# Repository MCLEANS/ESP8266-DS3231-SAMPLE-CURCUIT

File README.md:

# ESP8266-DS3231-SAMPLE-CURCUIT
A sample circuit for SMD ESP8266 and  DS3231 Implementation.

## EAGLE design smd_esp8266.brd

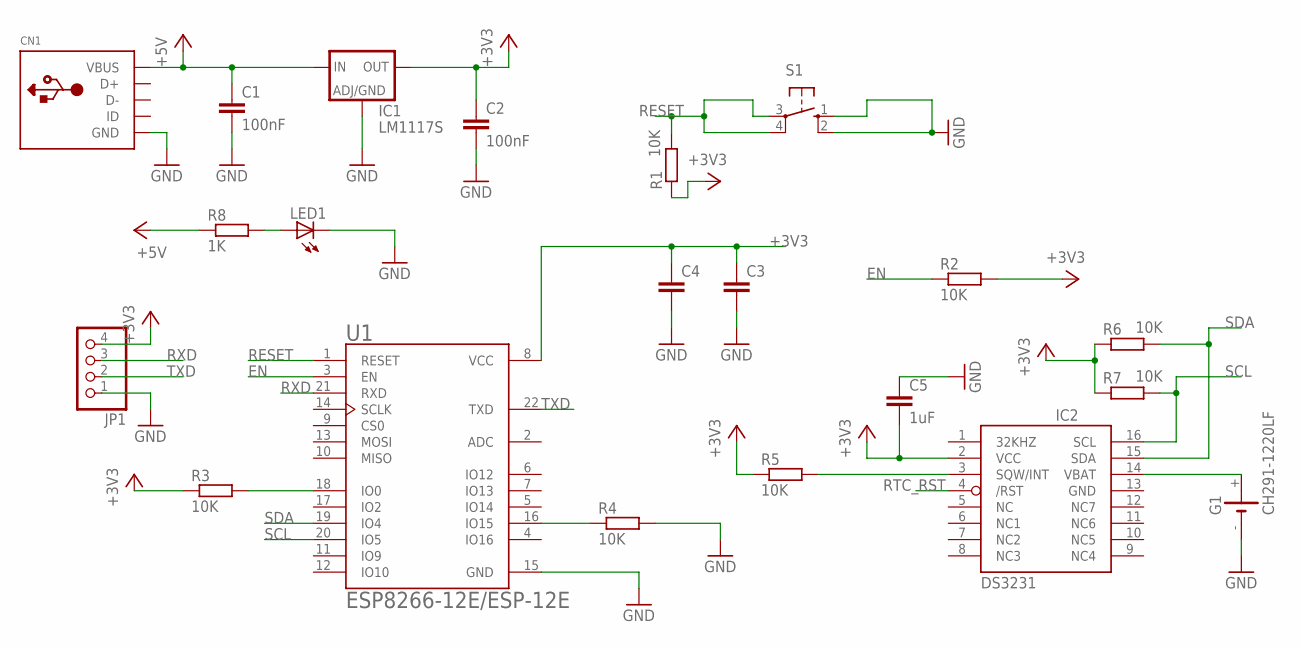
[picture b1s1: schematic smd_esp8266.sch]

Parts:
C1, C2: 100nF; C0805
C3, C4: C-EUC0805; C0805
C5: 1uF; C0805
CN1: USBMINIB; USB-MINIB
G1: CH291-1220LF
IC1: LM1117S; SOT223
IC2: DS3231/SO; SO16W
JP1: PINHD-1X4; 1X04
LED1: LEDCHIP-LED0805; CHIP-LED0805
R1, R2, R3, R4, R5, R6, R7: 10K; R0805
R8: 1K; R0805
S1: 10-XX; B3F-10XX
U1: ESP8266-12E/ESP-12E; XCVR_ESP8266-12E/ESP-12E

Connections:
+3V3: C2.1, C3.1, C4.1, C5.2, IC1.2 (OUT), IC1.4 (OUT), IC2.2 (VCC), JP1.4, R1.1, R2.2, R3.1, R5.1, R6.1, R7.1, U1.8 (VCC)
+5V: C1.1, CN1.VBUS, IC1.3 (IN), R8.1
EN: R2.1, U1.3 (EN)
GND: C1.2, C2.2, C3.2, C4.2, C5.1, CN1.GND, G1.-, IC1.1 (ADJ), IC2.13 (GND), JP1.1, LED1.C, R4.2, S1.1 (S), S1.2 (S1), U1.15 (GND)
unnamed: R3.2, U1.18 (IO0)
unnamed: R4.1, U1.16 (IO15)
unnamed: IC2.3 (SQW/INT), R5.2
unnamed: G1.+, IC2.14 (VBAT)
unnamed: LED1.A, R8.2
RESET: R1.2, S1.3, S1.4 (P1), U1.1 (RESET)
RTC_RST: IC2.4 (/RST)
RXD: JP1.3, U1.21 (RXD)
SCL: IC2.16 (SCL), R7.2, U1.20 (IO5)
SDA: IC2.15 (SDA), R6.2, U1.19 (IO4)
TXD: JP1.2, U1.22 (TXD)

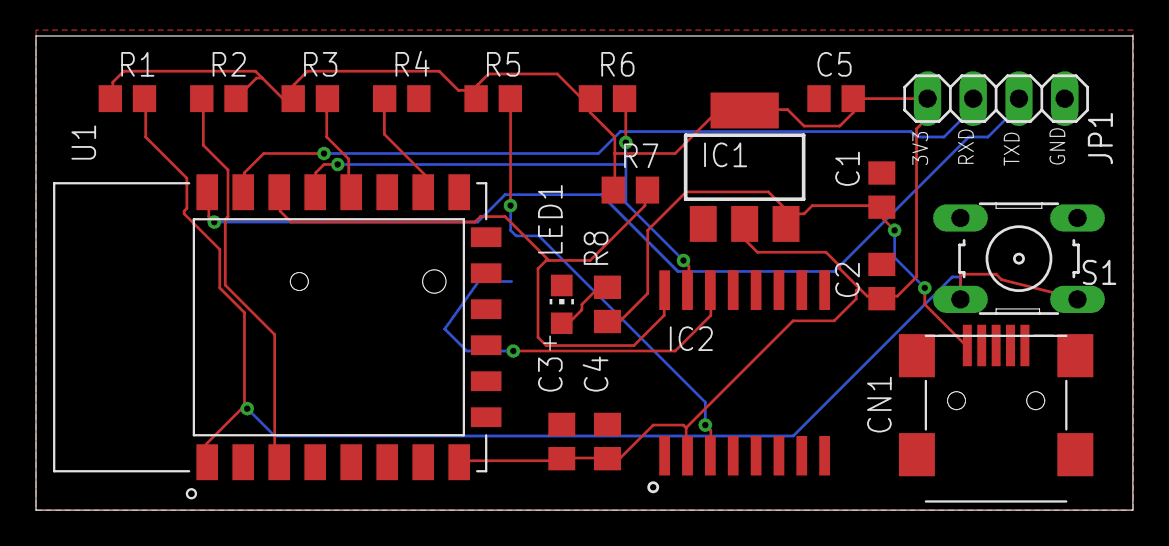
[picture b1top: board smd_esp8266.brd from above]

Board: 2 copper layers, 60.9 x 26.3 mm, 21 parts (1 on the bottom side), 14 nets.

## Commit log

2020-04-01 circuit board layout
2020-04-01 pulled up RTC interrupt pin
2020-04-01 updated decoupling capacitor values
2020-04-01 grounded top and bottom planes
2020-04-17 documentation
